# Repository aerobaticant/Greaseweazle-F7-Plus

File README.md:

# Greaseweazle-F7-Plus
My board design for [Keir Fraser's Greaseweazle](https://github.com/keirf/Greaseweazle).

The differences between this design and the original F7 are:

  * PCB 80mm x 50mm, KryoFlux form factor.
  * Added stronger buffers for driving 5.25" drives with higher current pull-up resistors.
  * Integrated 5V switching regulator, so only a single 12V supply is required for drives needing both rails.
  * Choice of full-size or micro USB connector.
  * USB ESD (electro-static discharge) protection.
  * Connections for external LEDs, for use if fitting the board in an enclosure.
  * Jumper link to select write protection by default.
  * Jumper link to disconnect WR_GATE for physical hardware level write protection.

This repository has only just been created.

Please check out the [Wiki](https://github.com/aerobaticant/Greaseweazle-F7-Plus/wiki) (under construction).

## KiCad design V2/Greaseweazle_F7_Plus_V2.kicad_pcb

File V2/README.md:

This is the folder containing the source files for my Greaseweazle V2 Plus board

Please note that this design is released using the Open Hardware licence.
https://www.oshwa.org/definition/

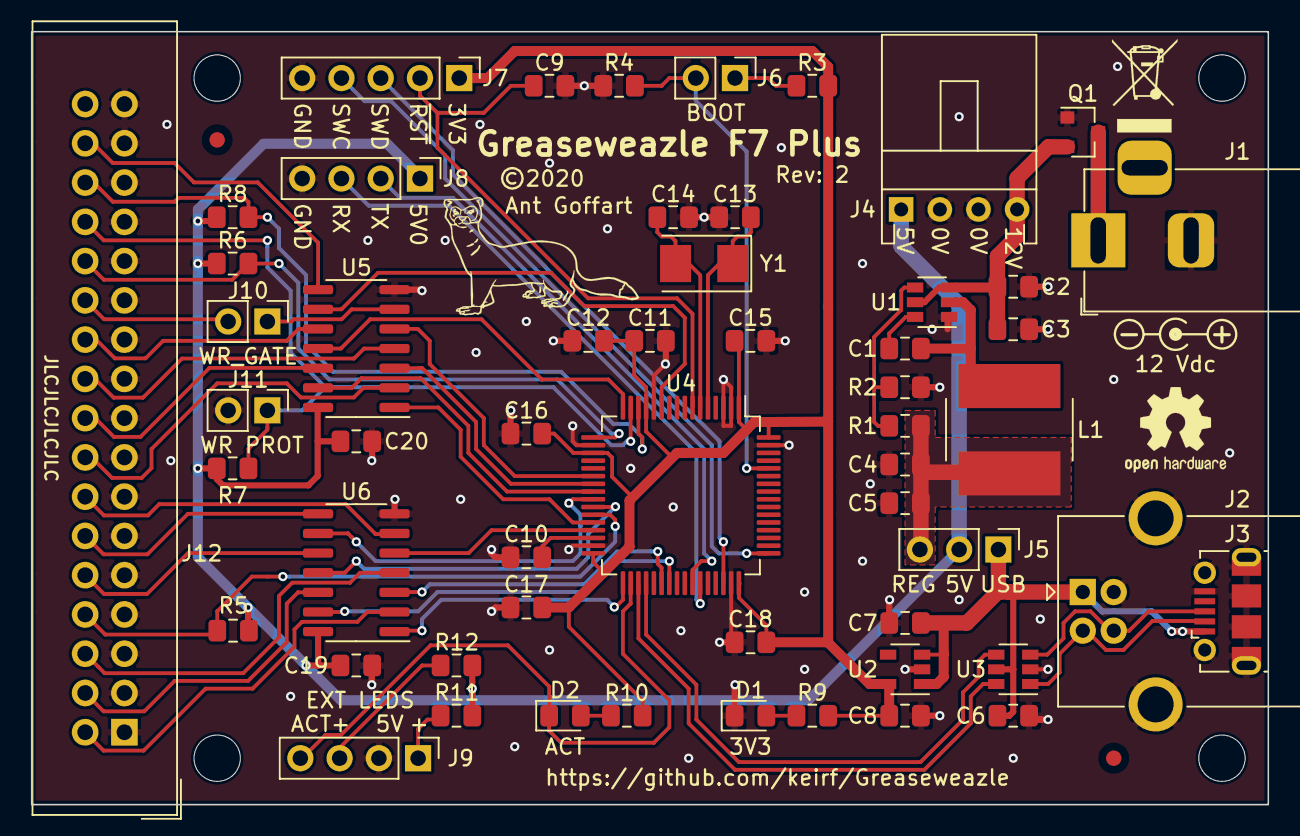
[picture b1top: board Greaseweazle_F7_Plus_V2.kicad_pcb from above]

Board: 2 copper layers, 80.0 x 50.0 mm, 65 parts (0 on the bottom side), 58 nets.

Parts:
C1, C6, C9, C12, C15, C16, C17, C18, C19, C20: 100N; C_0805_2012Metric_Pad1.15x1.40mm_HandSolder
C2, C3, C10: 10U; C_0805_2012Metric_Pad1.15x1.40mm_HandSolder
C4, C5: 22U; C_0805_2012Metric_Pad1.15x1.40mm_HandSolder
C7, C8, C11: 1U0; C_0805_2012Metric_Pad1.15x1.40mm_HandSolder
C13, C14: 27P; C_0805_2012Metric_Pad1.15x1.40mm_HandSolder
D1, D2: GREEN; LED_0805_2012Metric_Pad1.15x1.40mm_HandSolder
FID1, FID2: Fiducial; Fiducial_1mm_Mask2mm
G**: WEEE-Logo_4.2x6mm_SilkScreen
G**#2: Symbol_Barrel_Polarity
G**#3: Weasle; WeasleLogo
H1, H2, H3, H4: M3; MountingHole_3mm
J1: Wurth 694106301002; BarrelJack_Horizontal
J2: USB_B; USB_B_OST_USB-B1HSxx_Horizontal
J3: Molex 105017-1001; USB_Micro-B_Molex-105017-0001
J4: TE EI 171826-4; TE_171826-4_1x4_P2.50mm_Horizontal
J5: PIN1X3; PinHeader_1x03_P2.54mm_Vertical
J6, J10, J11: PIN1X2; PinHeader_1x02_P2.54mm_Vertical
J7: PIN1X5; PinHeader_1x05_P2.54mm_Vertical
J8, J9: PIN1X4; PinHeader_1x04_P2.54mm_Vertical
J12: IDC Box Header; IDC-Header_2x17_P2.54mm_Vertical
L1: SRN8040TA-4R7; L_Bourns_SRN8040TA
LOGO1: OSHW Logo; OSHW-Logo2_7.3x6mm_SilkScreen
Q1: Si2393DS; SOT-23
R1: 54K9; R_0805_2012Metric_Pad1.15x1.40mm_HandSolder
R2, R4: 10K0; R_0805_2012Metric_Pad1.15x1.40mm_HandSolder
R3, R5, R6, R7, R8: 1K0; R_0805_2012Metric_Pad1.15x1.40mm_HandSolder
R9, R10: 330R; R_0805_2012Metric_Pad1.15x1.40mm_HandSolder
R11, R12: 560R; R_0805_2012Metric_Pad1.15x1.40mm_HandSolder
U1: TPS562201DDC; SOT-23-6
U2: TLV75533PDBV; SOT-23-5
U3: USBLC6-2SC6; SOT-23-6
U4: STM32F730R8T6; LQFP-64_10x10mm_P0.5mm
U5, U6: 74LS07; SOIC-14_3.9x8.7mm_P1.27mm
Y1: 8.000MHz; Crystal_SMD_5032-2Pin_5.0x3.2mm

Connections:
+3V3: C8.1, C11.1, C12.1, C15.1, C16.1, C17.1, C18.1, J7.1, R3.1, R9.1, R10.1, U2.5, U4.1, U4.13, U4.19, U4.32, U4.48, U4.64
+5V: C19.1, C20.1, J4.1, J5.2, J8.1, R5.1, R6.1, R7.1, R8.1, R11.1, R12.1, U5.14, U6.14
+12V: C2.1, C3.1, J4.4, Q1.2, U1.3, U1.5
/5V_REG: C4.1, C5.1, J5.3, L1.2, R1.1
/ACT: D2.1, J9.4, U4.34
/BOOT: J6.2, R4.1, U4.60
/FB: R1.2, R2.1, U1.4
/OSC_IN: C13.1, U4.5, Y1.1
/OSC_OUT: C14.1, U4.6, Y1.2
/RX: J8.3, U4.43
/SW: C1.1, L1.1, U1.2
/SWCLK: J7.4, U4.49
/SWDIO: J7.3, U4.46
/TX: J8.2, U4.42
/USB_D+: U3.4, U4.36
/USB_D-: U3.6, U4.35
/USB_DIN+: J2.3, J3.3, U3.3
/USB_DIN-: J2.2, J3.2, U3.1
/USB_VBUS: C6.1, C7.1, J2.1, J3.1, J5.1, U2.1, U2.3, U3.5
/VCAP: C10.1, U4.30
/~DIR_5V~: J12.18, U5.12
/~DIR~: U4.24, U5.13
/~DS0_5V~: J12.14, U6.6
/~DS0~: U4.29, U6.5
/~DS1_5V~: J12.12, U6.8
/~DS1~: U4.25, U6.9
/~INDEX~: J12.8, R5.2, U4.27
/~M0_5V~: J12.10, U6.10
/~M0~: U4.26, U6.11
/~M1_5V~: J12.16, U5.2
/~M1~: U4.28, U5.1
/~PIN2_5V~: J12.2, U6.2
/~PIN2~: U4.33, U6.1
/~PIN4_5V~: J12.4, U6.12
/~PIN4~: U4.39, U6.13
/~PIN6_5V~: J12.6, U6.4
/~PIN6~: U4.38, U6.3
/~RD_DAT~: J12.30, R8.2, U4.14
/~RST~: C9.1, J7.2, U4.7
/~SIDE_5V~: J12.32, U5.8
/~SIDE~: U4.11, U5.9
/~STEP_5V~: J12.20, U5.4
/~STEP~: U4.23, U5.3
/~TRK_00~: J12.26, R6.2, U4.17
/~WR_DAT_5V~: J12.22, U5.10
/~WR_DAT~: U4.16, U5.11
/~WR_GATE_5V~: J10.2, J12.24
/~WR_GATE~: U4.22, U5.5
/~WR_PROT~: J11.1, J12.28, R7.2, U4.15
GND: C2.2, C3.2, C4.2, C5.2, C6.2, C7.2, C8.2, C9.2, C10.2, C11.2, C12.2, C13.2, C14.2, C15.2, C16.2, C17.2, C18.2, C19.2, C20.2, D1.1, J1.2, J2.4, J2.5, J3.5, J3.6, J4.2, J4.3, J7.5, J8.4, J9.2, J11.2, J12.1, J12.3, J12.5, J12.7, J12.9, J12.11, J12.13, J12.15, J12.17, J12.19, J12.21, J12.23, J12.25, J12.27, J12.29, J12.31, J12.33, Q1.1, R2.2, R4.2, U1.1, U2.2, U3.2, U4.2, U4.3, U4.12, U4.18, U4.31, U4.47, U4.63, U5.7, U6.7
unnamed: C1.2, U1.6
unnamed: D1.2, R9.2
unnamed: D2.2, R10.2
unnamed: J1.1, Q1.3
unnamed: J6.1, R3.2
unnamed: J9.1, R11.2
unnamed: J9.3, R12.2
unnamed: J10.1, U5.6

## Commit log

2020-05-27 Changed README.md to markdown
2020-06-12 Added schematic and image
2020-06-28 Add all V2 files
2020-06-28 Update README.md
    Add OSHW licence link
2020-07-10 Add V2 inage
2020-08-27 Fix typo
2021-04-01 Added CSV BOM file

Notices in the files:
V2/Greaseweazle_F7_Plus_V2.kicad_pcb:
©2020
